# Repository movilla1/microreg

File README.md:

# microreg
"Micro" voltage regulator to be used on a mini glider plane, for the engineless category.

This voltage regulator was created so it can be assembled with the components available on the argentinian market, specially in Cordoba, where I live, it can certainly be done smaller if you use double sided boards and smaller smd components but that also increases the price and it was created to be good, cheap and reliable :-) goals that were archieved, about 5 of this units were sold and currently is not being produced anymore.

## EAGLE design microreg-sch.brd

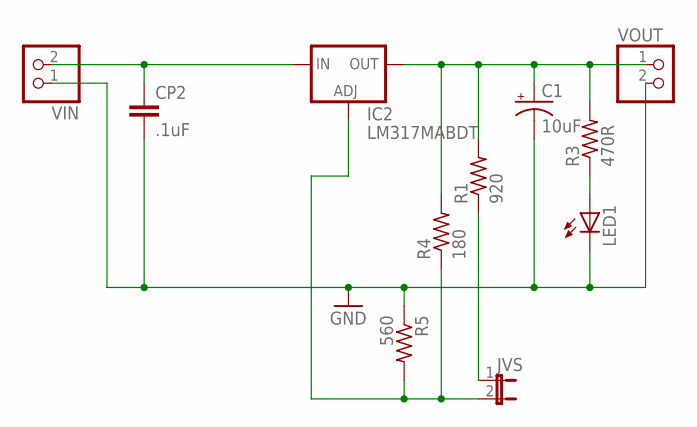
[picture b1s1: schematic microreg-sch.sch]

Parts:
C1: 10uF; E2,5-5
CP2: .1uF; C1206
IC2: LM317MABDT; DPACK
JVS: JP1E; JP1
LED1: LEDCHIPLED_1206; CHIPLED_1206
R1: 920; R1206
R3: 470R; M1206
R4: 180; M1206
R5: 560; M1206
VIN: PINHD-1X2; 1X02
VOUT: PINHD-1X2; 1X02

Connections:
GND: C1.-, CP2.2, LED1.C, R5.1, VIN.1, VOUT.2
unnamed: CP2.1, IC2.3 (IN), VIN.2
unnamed: JVS.1, R1.1
unnamed: IC2.1 (ADJ), JVS.2, R4.1, R5.2
unnamed: LED1.A, R3.1
unnamed: C1.+, IC2.4 (OUT), R1.2, R3.2, R4.2, VOUT.1

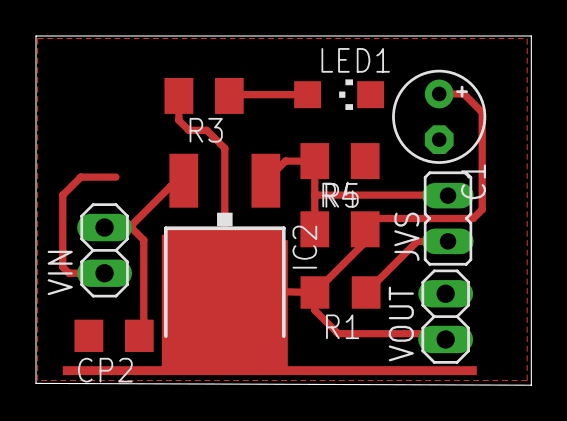
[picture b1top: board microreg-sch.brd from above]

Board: 2 copper layers, 27.5 x 19.4 mm, 11 parts (0 on the bottom side), 6 nets.

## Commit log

2017-03-10 Add files via upload
    Working version, as used on the last assembly made.
2017-03-10 Update README.md
    new/complete description on the readme.
